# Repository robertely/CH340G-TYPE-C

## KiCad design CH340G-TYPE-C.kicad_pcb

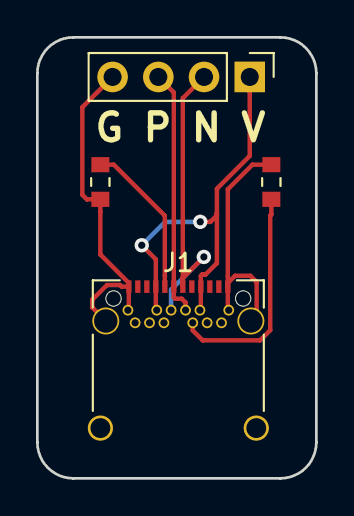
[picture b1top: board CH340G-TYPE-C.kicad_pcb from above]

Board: 2 copper layers, 15.5 x 24.5 mm, 4 parts (0 on the bottom side), 6 nets.

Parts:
J1: USB_C_Receptacle; USB_C_Receptacle_CUI_UJ31-CH-31-SMT-TR_CircularHoles
J2: Conn_01x04; PinHeader_1x04_P2.54mm_Vertical
R1, R2: 5K1; R_0603_1608Metric_Pad0.84x1.00mm_HandSolder

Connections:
GND: J1.A1, J1.A12, J1.B1, J1.B12, J1.S1, J2.4, R1.2, R2.2
unnamed: J1.A5, R2.1
unnamed: J1.A6, J1.B6, J2.3
unnamed: J1.A7, J1.B7, J2.2
unnamed: J1.B5, R1.1
VCC: J1.A4, J1.A9, J1.B4, J1.B9, J2.1

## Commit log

2018-02-28 init
2018-02-28 Create LICENSE
